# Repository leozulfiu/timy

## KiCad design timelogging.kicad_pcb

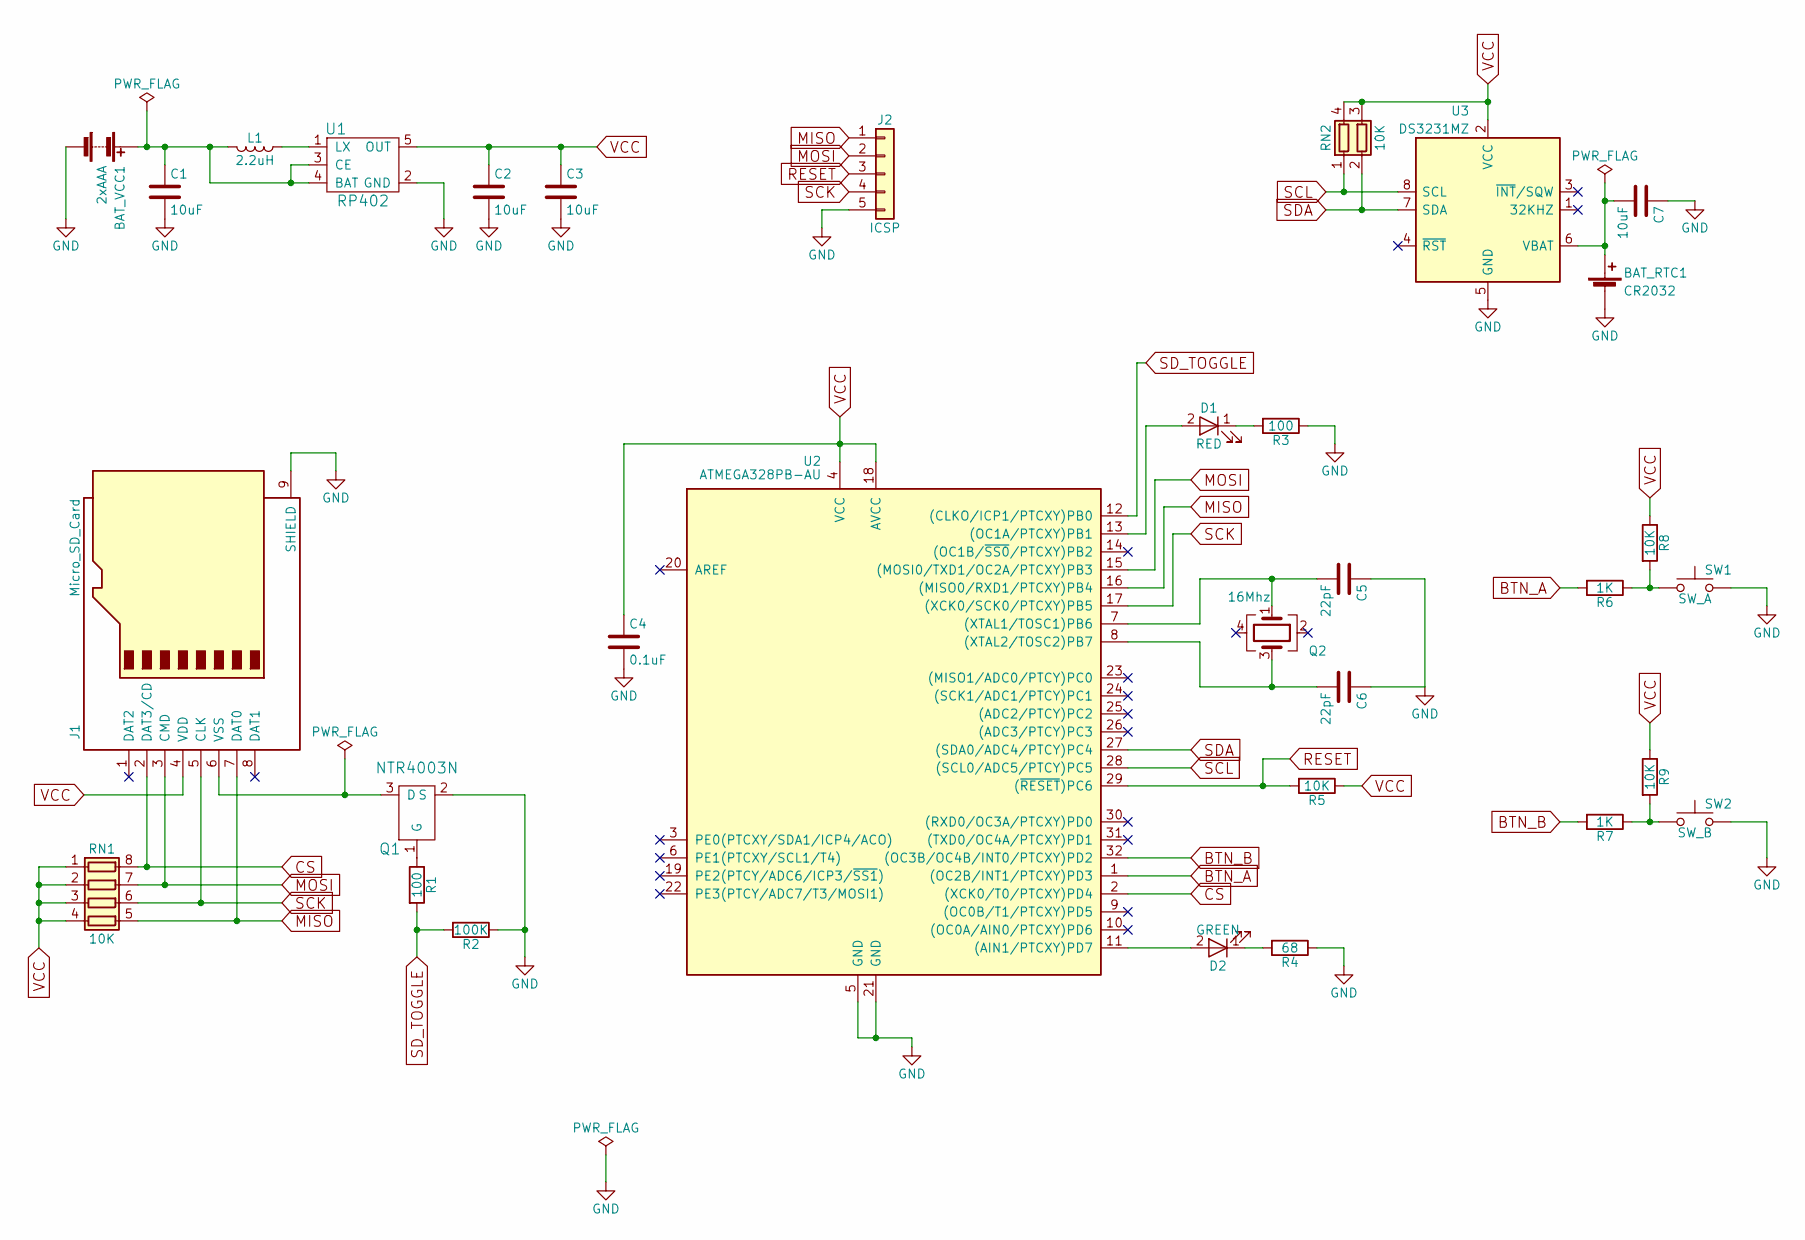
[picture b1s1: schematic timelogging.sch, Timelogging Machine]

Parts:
BAT_RTC1: CR2032; Keystone_1058_1x2032-CoinCell
BAT_VCC1: 2xAAA; Keystone_2468_2xAAA
C1, C2, C3: 10uF; C_0603
C4: 0.1uF; C_0805
C5, C6: 22pF; C_0805
C7: 10uF; C_0805
D1: RED; LED_1206
D2: GREEN; LED_1206
J1: Micro_SD_Card; Hirose_DM3D-SF
J2: ICSP; Pin_Header_Straight_1x05_Pitch2.54mm_SMD_Pin1Left
L1: 2.2uH; L_Taiyo-Yuden_NR-50xx
Q1: NTR4003N; SOT-23
Q2: 16Mhz; Crystal_SMD_3225-4pin_3.2x2.5mm
R1, R3: 100; R_0805
R2: 100K; R_0805
R4: 68; R_0805
R5, R8, R9: 10K; R_0805
R6, R7: 1K; R_0805
RN1: 10K; R_Array_Convex_4x0603; Mouser Part 774-742C083103JP
RN2: 10K; R_Array_Convex_2x0603; Mouser nr 774-742C043103JP
SW1: SW_A; SW_SPST_B3S-1000
SW2: SW_B; SW_SPST_B3S-1000
U1: RP402; SOT-23-5
U2: ATMEGA328PB-AU; TQFP-32_7x7mm_Pitch0.8mm
U3: DS3231MZ; SOIC-8_3.9x4.9mm_Pitch1.27mm

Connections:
BTN_A: R6.2, U2.1 ((OC2B/INT1/PTCXY)PD3)
BTN_B: R7.2, U2.32 ((OC3B/OC4B/INT0/PTCXY)PD2)
CS: J1.2 (DAT3/CD), RN1.8 (R1.2), U2.2 ((XCK0/T0/PTCXY)PD4)
GND: BAT_RTC1.2 (-), BAT_VCC1.2 (-), C1.2, C2.2, C3.2, C4.2, C5.1, C6.1, C7.1, J1.9 (SHIELD), J2.5, Q1.2 (S), R2.1, R3.1, R4.1, SW1.2, SW2.2, U1.2 (GND), U2.5 (GND), U2.21 (GND), U3.5 (GND)
MISO: J1.7 (DAT0), J2.1, RN1.5 (R4.2), U2.16 ((MISO0/RXD1/PTCXY)PB4)
MOSI: J1.3 (CMD), J2.2, RN1.7 (R2.2), U2.15 ((MOSI0/TXD1/OC2A/PTCXY)PB3)
unnamed: BAT_RTC1.1 (+), C7.2, U3.6 (VBAT)
unnamed: BAT_VCC1.1 (+), C1.1, L1.2, U1.3 (CE), U1.4 (BAT)
unnamed: C5.2, Q2.1, U2.7 ((XTAL1/TOSC1)PB6)
unnamed: C6.2, Q2.3, U2.8 ((XTAL2/TOSC2)PB7)
unnamed: D1.1 (K), R3.2
unnamed: D1.2 (A), U2.13 ((OC1A/PTCXY)PB1)
unnamed: D2.1 (K), R4.2
unnamed: D2.2 (A), U2.11 ((AIN1/PTCXY)PD7)
unnamed: J1.6 (VSS), Q1.3 (D)
unnamed: L1.1, U1.1 (LX)
unnamed: Q1.1 (G), R1.1
unnamed: R6.1, R8.2, SW1.1
unnamed: R7.1, R9.2, SW2.1
RESET: J2.3, R5.2, U2.29 ((~RESET~)PC6)
SCK: J1.5 (CLK), J2.4, RN1.6 (R3.2), U2.17 ((XCK0/SCK0/PTCXY)PB5)
SCL: RN2.1 (R1.1), U2.28 ((SCL0/ADC5/PTCY)PC5), U3.8 (SCL)
SDA: RN2.2 (R2.1), U2.27 ((SDA0/ADC4/PTCY)PC4), U3.7 (SDA)
SD_TOGGLE: R1.2, R2.2, U2.12 ((CLKO/ICP1/PTCXY)PB0)
VCC: C2.1, C3.1, C4.1, J1.4 (VDD), R5.1, R8.1, R9.1, RN1.1 (R1.1), RN1.2 (R2.1), RN1.3 (R3.1), RN1.4 (R4.1), RN2.3 (R2.2), RN2.4 (R1.2), U1.5 (OUT), U2.4 (VCC), U2.18 (AVCC), U3.2 (VCC)

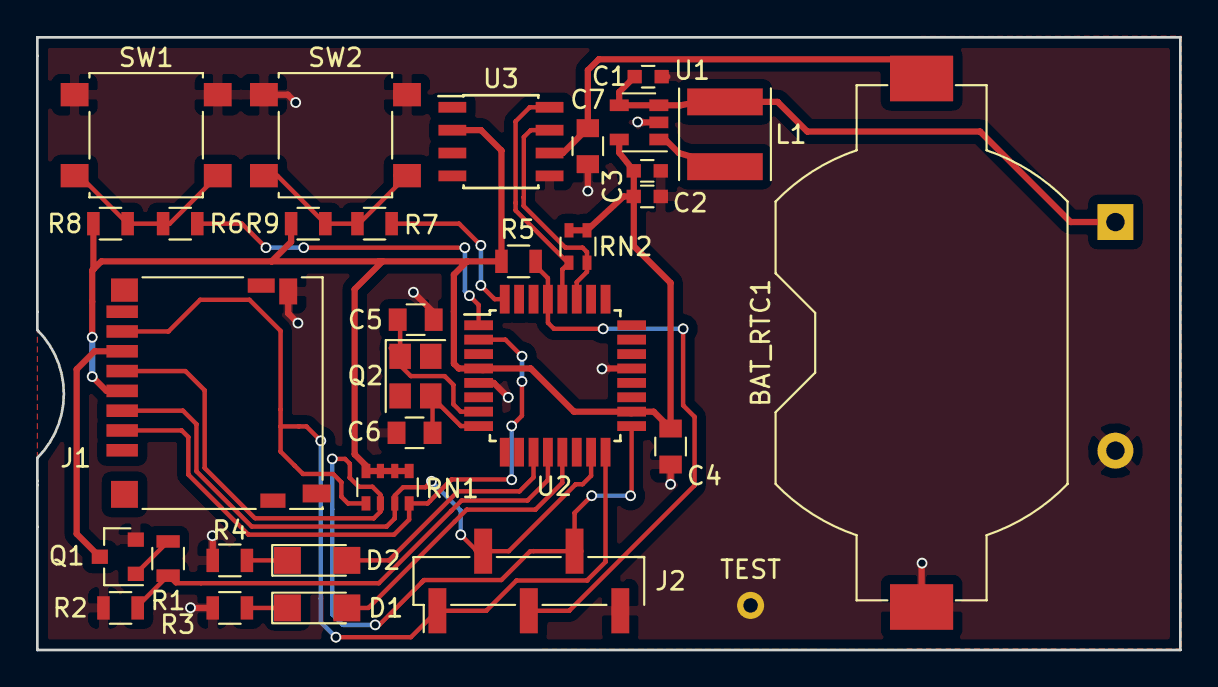
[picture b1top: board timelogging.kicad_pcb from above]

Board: 2 copper layers, 63.5 x 34.0 mm, 33 parts (1 on the bottom side), 25 nets.

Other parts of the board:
TEST: Measurement_Point_Round-TH_Small

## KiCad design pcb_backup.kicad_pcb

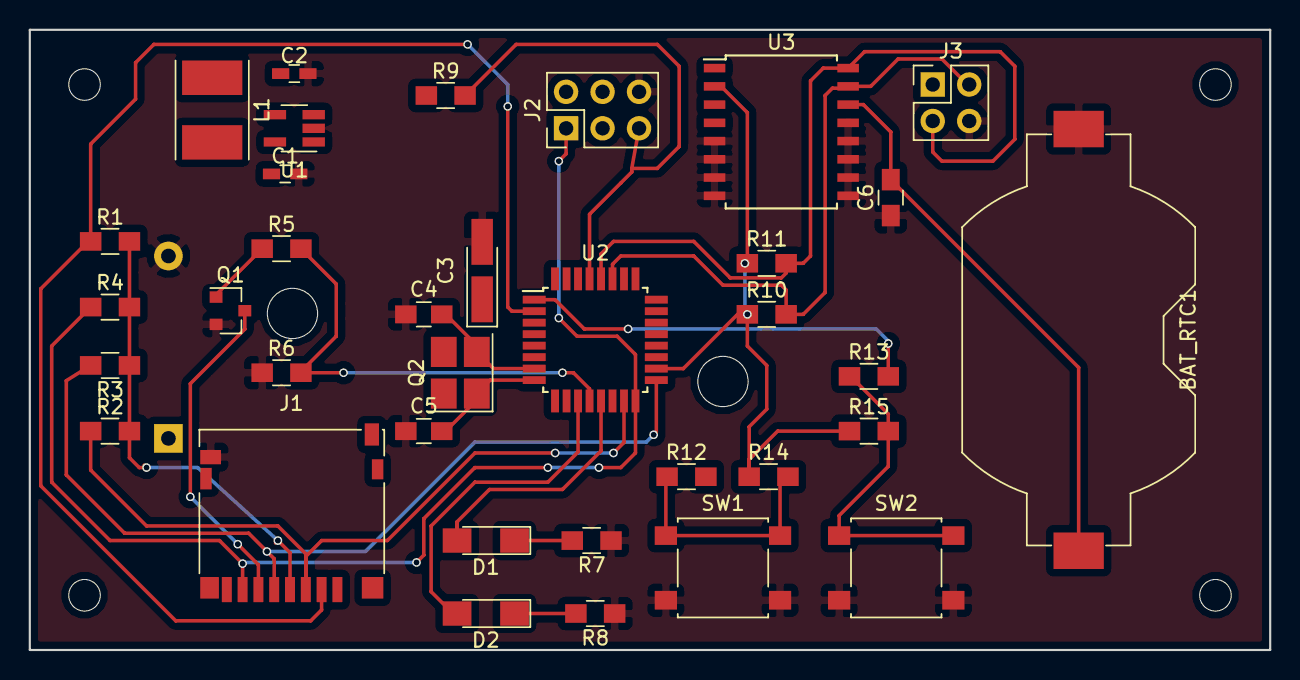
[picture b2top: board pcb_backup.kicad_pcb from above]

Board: 2 copper layers, 86.4 x 43.2 mm, 36 parts (1 on the bottom side), 25 nets.

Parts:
BAT_RTC1: CR2032; Keystone_1058_1x2032-CoinCell
BAT_VCC1: 2xAAA; Keystone_2468_2xAAA
C1, C2: 10uF; C_0603_HandSoldering
C3: 0.1uF; CP_Tantalum_Case-A_EIA-3216-18_Hand
C4, C5: 22pF; C_0805_HandSoldering
C6: 10uF; C_0805_HandSoldering
D1: RED; LED_1206_HandSoldering
D2: GREEN; LED_1206_HandSoldering
J1: Micro_SD_Card; Hirose_DM3D-SF
J2: ICSP; Pin_Header_Straight_2x03_Pitch2.54mm
J3: RTC_ICSP; Pin_Header_Straight_2x02_Pitch2.54mm
L1: 2.2uH; L_Taiyo-Yuden_NR-50xx_HandSoldering
Q1: 2N7002; SOT-23
Q2: 16Mhz; Crystal_SMD_3225-4pin_3.2x2.5mm_HandSoldering
R1, R2, R3, R4, R9, R10, R11, R14, R15: 10K; R_0805_HandSoldering
R5: 10; R_0805_HandSoldering
R6: 100K; R_0805_HandSoldering
R7: 100; R_0805_HandSoldering
R8: 68; R_0805_HandSoldering
R12, R13: 1K; R_0805_HandSoldering
SW1: SW_A; SW_SPST_B3S-1000
SW2: SW_B; SW_SPST_B3S-1000
U1: RP402; SOT-23-5_HandSoldering
U2: ATMEGA328P-PU; TQFP-32_7x7mm_Pitch0.8mm
U3: DS3231; SOIC-16W_7.5x10.3mm_Pitch1.27mm

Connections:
BTN_A: R12.2, U2.32
BTN_B: R13.2, U2.1
CS: J1.2, R1.1, U2.2
GND: BAT_RTC1.2, BAT_VCC1.2, C1.2, C2.2, C3.2, C4.1, C5.1, C6.1, J1.9, J2.6, J3.4, Q1.2, R6.1, R7.1, R8.1, SW1.2, SW2.2, U1.2, U2.3, U2.5, U2.21, U3.5, U3.6, U3.7, U3.8, U3.9, U3.10, U3.11, U3.12, U3.13
MISO: J1.7, J2.1, R4.1, U2.16
MOSI: J1.3, J2.4, R2.1, U2.15
unnamed: BAT_RTC1.1, C6.2, U3.14
unnamed: BAT_VCC1.1, C1.1, L1.2, U1.4
unnamed: C4.2, Q2.2, U2.7
unnamed: C5.2, Q2.1, U2.8
unnamed: D1.1, R7.2
unnamed: D1.2, U2.13
unnamed: D2.1, R8.2
unnamed: D2.2, U2.11
unnamed: J1.6, Q1.3
unnamed: L1.1, U1.1
unnamed: Q1.1, R5.1
unnamed: R12.1, R14.2, SW1.1
unnamed: R13.1, R15.2, SW2.1
RESET: J2.5, R9.2, U2.29
SCK: J1.5, J2.3, R3.2, U2.17
SCL: J3.3, R11.2, U2.28, U3.16
SDA: J3.2, R10.2, U2.27, U3.15
SD_TOGGLE: R5.2, R6.2, U2.12
VCC: C2.1, C3.1, J1.4, R1.2, R2.2, R3.1, R4.2, R9.1, R10.1, R11.1, R14.1, R15.1, U1.3, U1.5, U2.4, U2.6, U2.18, U3.2

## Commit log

2018-01-13 improve power circuit
2018-02-19 rework schematic
2018-03-15 redo pcb design
